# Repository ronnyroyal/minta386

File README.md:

# Minta 386 memory board

This is a reverse engineered memory board for the Minta Technologies PCB-305 Mainboard.  
https://theretroweb.com/motherboards/s/minta-technologies-co-pcb-305  
  
I bought this board a while ago missing it's proprietary memory board with the plan to reverse engineer the memory board.   
The memory card was designed with sipp memory in mind as i have a lot of sipp modules, but the spacing also allows for simm sockets to be installed.
 
It can accomodate up to 8 1MB modules with the slot being wired to theoretically support up to 16MB.  
The first PCB revision contains a fault with the parity bit lines being swapped. This is fixed in the provided files.

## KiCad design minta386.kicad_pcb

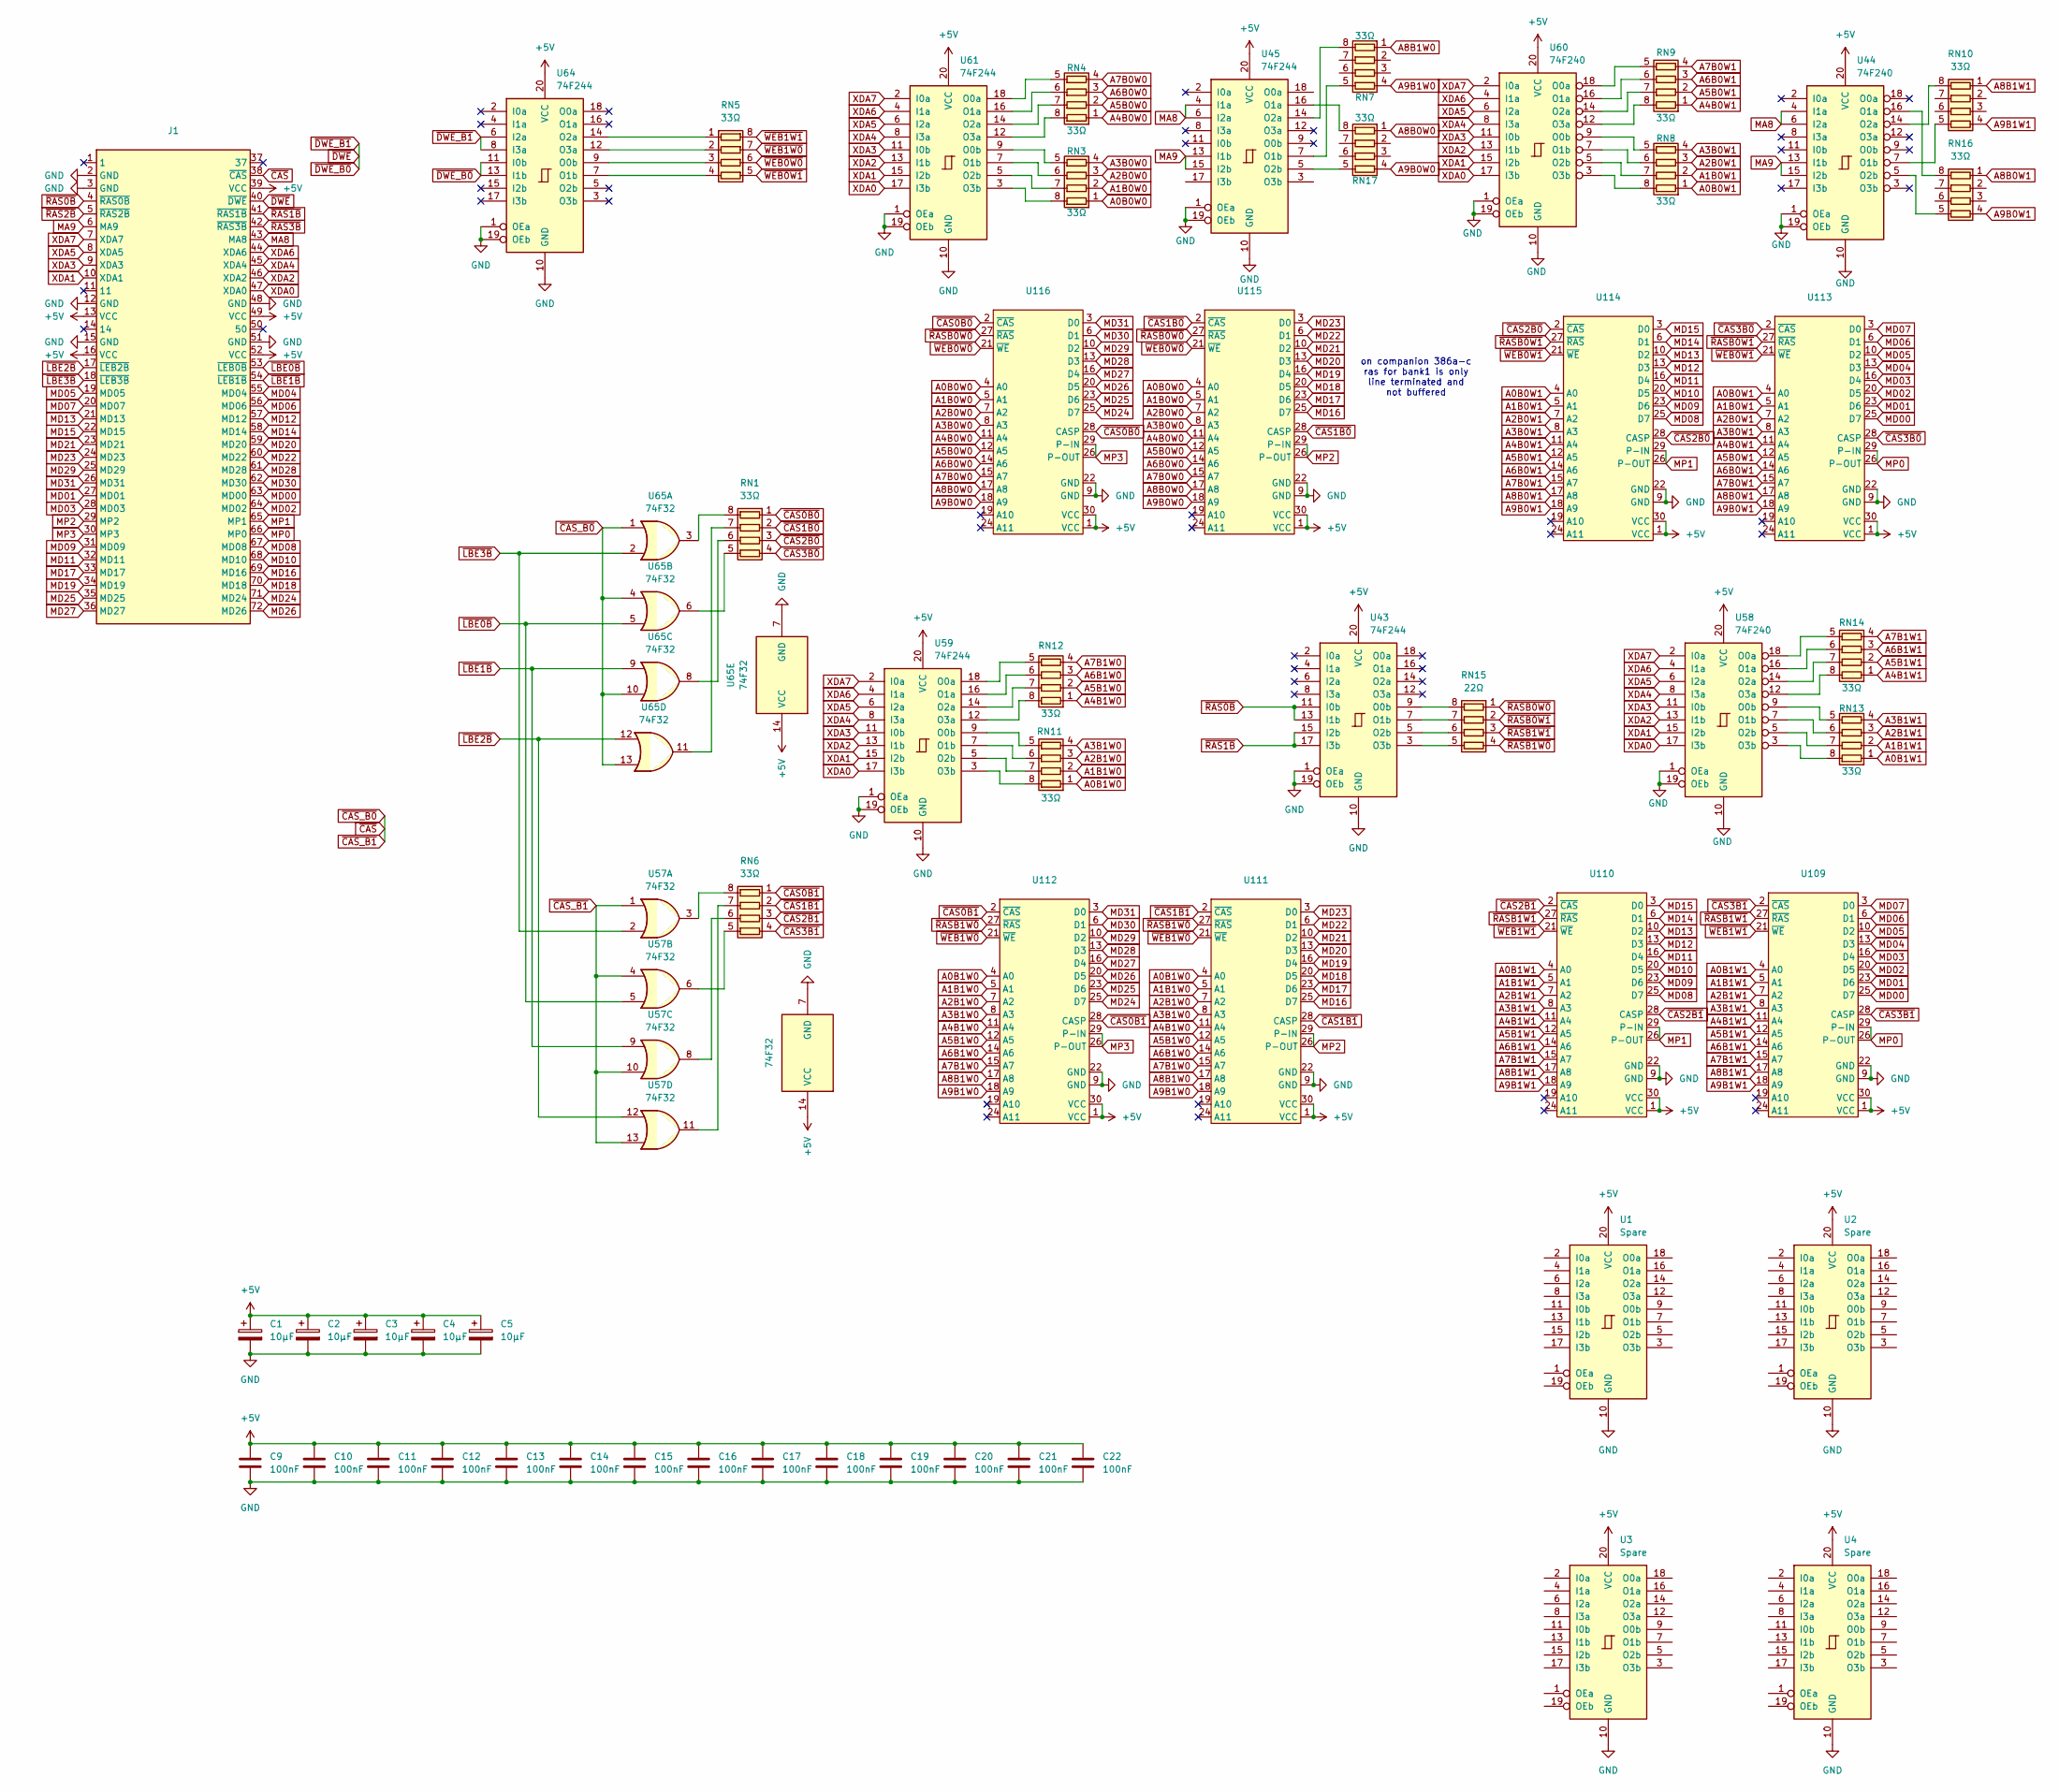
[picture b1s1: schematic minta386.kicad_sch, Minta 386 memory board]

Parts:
C1, C2, C3, C4, C5: 10µF; CP_EIA-6032-28_Kemet-C_Pad2.25x2.35mm_HandSolder
C9, C10, C11, C12, C13, C14, C15, C16, C17, C18, C19, C20, C21, C22: 100nF; C_0805_2012Metric_Pad1.18x1.45mm_HandSolder
J1: minta_386_memory_bus
RN1, RN3, RN4, RN5, RN6, RN7, RN8, RN9, RN10, RN11, RN12, RN13, RN14, RN16, RN17: 33Ω; R_Array_Concave_4x0603
RN15: 22Ω; R_Array_Concave_4x0603
U1, U2, U3, U4: Spare; SOIC-20W_7.5x12.8mm_P1.27mm
U43, U45, U59, U61, U64: 74F244; SOIC-20W_7.5x12.8mm_P1.27mm
U44, U58, U60: 74F240; SOIC-20W_7.5x12.8mm_P1.27mm
U57, U65: 74F32; SOIC-14_3.9x8.7mm_P1.27mm
U109, U110, U111, U112, U113, U114, U115, U116: PinSocket_1x30_P2.54mm_Vertical

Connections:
+5V: C1.1, C2.1, C3.1, C4.1, C5.1, C9.1, C10.1, C11.1, C12.1, C13.1, C14.1, C15.1, C16.1, C17.1, C18.1, C19.1, C20.1, C21.1, C22.1, J1.13 (VCC), J1.16 (VCC), J1.39 (VCC), J1.49 (VCC), J1.52 (VCC), U1.20 (VCC), U2.20 (VCC), U3.20 (VCC), U4.20 (VCC), U43.20 (VCC), U44.20 (VCC), U45.20 (VCC), U57.14 (VCC), U58.20 (VCC), U59.20 (VCC), U60.20 (VCC), U61.20 (VCC), U64.20 (VCC), U65.14 (VCC), U109.1 (VCC), U109.30 (VCC), U110.1 (VCC), U110.30 (VCC), U111.1 (VCC), U111.30 (VCC), U112.1 (VCC), U112.30 (VCC), U113.1 (VCC), U113.30 (VCC), U114.1 (VCC), U114.30 (VCC), U115.1 (VCC), U115.30 (VCC), U116.1 (VCC), U116.30 (VCC)
A0B0W0: RN3.1 (R1.1), U115.4 (A0), U116.4 (A0)
A0B0W1: RN8.1 (R1.1), U113.4 (A0), U114.4 (A0)
A0B1W0: RN11.1 (R1.1), U111.4 (A0), U112.4 (A0)
A0B1W1: RN13.1 (R1.1), U109.4 (A0), U110.4 (A0)
A1B0W0: RN3.2 (R2.1), U115.5 (A1), U116.5 (A1)
A1B0W1: RN8.2 (R2.1), U113.5 (A1), U114.5 (A1)
A1B1W0: RN11.2 (R2.1), U111.5 (A1), U112.5 (A1)
A1B1W1: RN13.2 (R2.1), U109.5 (A1), U110.5 (A1)
A2B0W0: RN3.3 (R3.1), U115.7 (A2), U116.7 (A2)
A2B0W1: RN8.3 (R3.1), U113.7 (A2), U114.7 (A2)
A2B1W0: RN11.3 (R3.1), U111.7 (A2), U112.7 (A2)
A2B1W1: RN13.3 (R3.1), U109.7 (A2), U110.7 (A2)
A3B0W0: RN3.4 (R4.1), U115.8 (A3), U116.8 (A3)
A3B0W1: RN8.4 (R4.1), U113.8 (A3), U114.8 (A3)
A3B1W0: RN11.4 (R4.1), U111.8 (A3), U112.8 (A3)
A3B1W1: RN13.4 (R4.1), U109.8 (A3), U110.8 (A3)
A4B0W0: RN4.1 (R1.1), U115.11 (A4), U116.11 (A4)
A4B0W1: RN9.1 (R1.1), U113.11 (A4), U114.11 (A4)
A4B1W0: RN12.1 (R1.1), U111.11 (A4), U112.11 (A4)
A4B1W1: RN14.1 (R1.1), U109.11 (A4), U110.11 (A4)
A5B0W0: RN4.2 (R2.1), U115.12 (A5), U116.12 (A5)
A5B0W1: RN9.2 (R2.1), U113.12 (A5), U114.12 (A5)
A5B1W0: RN12.2 (R2.1), U111.12 (A5), U112.12 (A5)
A5B1W1: RN14.2 (R2.1), U109.12 (A5), U110.12 (A5)
A6B0W0: RN4.3 (R3.1), U115.14 (A6), U116.14 (A6)
A6B0W1: RN9.3 (R3.1), U113.14 (A6), U114.14 (A6)
A6B1W0: RN12.3 (R3.1), U111.14 (A6), U112.14 (A6)
A6B1W1: RN14.3 (R3.1), U109.14 (A6), U110.14 (A6)
A7B0W0: RN4.4 (R4.1), U115.15 (A7), U116.15 (A7)
A7B0W1: RN9.4 (R4.1), U113.15 (A7), U114.15 (A7)
A7B1W0: RN12.4 (R4.1), U111.15 (A7), U112.15 (A7)
A7B1W1: RN14.4 (R4.1), U109.15 (A7), U110.15 (A7)
A8B0W0: RN17.1 (R1.1), U115.17 (A8), U116.17 (A8)
A8B0W1: RN16.1 (R1.1), U113.17 (A8), U114.17 (A8)
A8B1W0: RN7.1 (R1.1), U111.17 (A8), U112.17 (A8)
A8B1W1: RN10.1 (R1.1), U109.17 (A8), U110.17 (A8)
A9B0W0: RN17.4 (R4.1), U115.18 (A9), U116.18 (A9)
A9B0W1: RN16.4 (R4.1), U113.18 (A9), U114.18 (A9)
A9B1W0: RN7.4 (R4.1), U111.18 (A9), U112.18 (A9)
A9B1W1: RN10.4 (R4.1), U109.18 (A9), U110.18 (A9)
GND: C1.2, C2.2, C3.2, C4.2, C5.2, C9.2, C10.2, C11.2, C12.2, C13.2, C14.2, C15.2, C16.2, C17.2, C18.2, C19.2, C20.2, C21.2, C22.2, J1.2 (GND), J1.3 (GND), J1.12 (GND), J1.15 (GND), J1.48 (GND), J1.51 (GND), U1.10 (GND), U2.10 (GND), U3.10 (GND), U4.10 (GND), U43.1 (OEa), U43.10 (GND), U43.19 (OEb), U44.1 (OEa), U44.10 (GND), U44.19 (OEb), U45.1 (OEa), U45.10 (GND), U45.19 (OEb), U57.7 (GND), U58.1 (OEa), U58.10 (GND), U58.19 (OEb), U59.1 (OEa), U59.10 (GND), U59.19 (OEb), U60.1 (OEa), U60.10 (GND), U60.19 (OEb), U61.1 (OEa), U61.10 (GND), U61.19 (OEb), U64.1 (OEa), U64.10 (GND), U64.19 (OEb), U65.7 (GND), U109.9 (GND), U109.22 (GND), U110.9 (GND), U110.22 (GND), U111.9 (GND), U111.22 (GND), U112.9 (GND), U112.22 (GND), U113.9 (GND), U113.22 (GND), U114.9 (GND), U114.22 (GND), U115.9 (GND), U115.22 (GND), U116.9 (GND), U116.22 (GND)
MA8: J1.43 (MA8), U44.4 (I1a), U44.6 (I2a), U45.4 (I1a), U45.6 (I2a)
MA9: J1.6 (MA9), U44.13 (I1b), U44.15 (I2b), U45.13 (I1b), U45.15 (I2b)
MD00: J1.63 (MD00), U109.25 (D7), U113.25 (D7)
MD01: J1.27 (MD01), U109.23 (D6), U113.23 (D6)
MD02: J1.64 (MD02), U109.20 (D5), U113.20 (D5)
MD03: J1.28 (MD03), U109.16 (D4), U113.16 (D4)
MD04: J1.55 (MD04), U109.13 (D3), U113.13 (D3)
MD05: J1.19 (MD05), U109.10 (D2), U113.10 (D2)
MD06: J1.56 (MD06), U109.6 (D1), U113.6 (D1)
MD07: J1.20 (MD07), U109.3 (D0), U113.3 (D0)
MD08: J1.67 (MD08), U110.25 (D7), U114.25 (D7)
MD09: J1.31 (MD09), U110.23 (D6), U114.23 (D6)
MD10: J1.68 (MD10), U110.20 (D5), U114.20 (D5)
MD11: J1.32 (MD11), U110.16 (D4), U114.16 (D4)
MD12: J1.57 (MD12), U110.13 (D3), U114.13 (D3)
MD13: J1.21 (MD13), U110.10 (D2), U114.10 (D2)
MD14: J1.58 (MD14), U110.6 (D1), U114.6 (D1)
MD15: J1.22 (MD15), U110.3 (D0), U114.3 (D0)
MD16: J1.69 (MD16), U111.25 (D7), U115.25 (D7)
MD17: J1.33 (MD17), U111.23 (D6), U115.23 (D6)
MD18: J1.70 (MD18), U111.20 (D5), U115.20 (D5)
MD19: J1.34 (MD19), U111.16 (D4), U115.16 (D4)
MD20: J1.59 (MD20), U111.13 (D3), U115.13 (D3)
MD21: J1.23 (MD21), U111.10 (D2), U115.10 (D2)
MD22: J1.60 (MD22), U111.6 (D1), U115.6 (D1)
MD23: J1.24 (MD23), U111.3 (D0), U115.3 (D0)
MD24: J1.71 (MD24), U112.25 (D7), U116.25 (D7)
MD25: J1.35 (MD25), U112.23 (D6), U116.23 (D6)
MD26: J1.72 (MD26), U112.20 (D5), U116.20 (D5)
MD27: J1.36 (MD27), U112.16 (D4), U116.16 (D4)
MD28: J1.61 (MD28), U112.13 (D3), U116.13 (D3)
MD29: J1.25 (MD29), U112.10 (D2), U116.10 (D2)
MD30: J1.62 (MD30), U112.6 (D1), U116.6 (D1)
MD31: J1.26 (MD31), U112.3 (D0), U116.3 (D0)
MP0: J1.66 (MP0), U109.26 (P-OUT), U109.29 (P-IN), U113.26 (P-OUT), U113.29 (P-IN)
MP1: J1.65 (MP1), U110.26 (P-OUT), U110.29 (P-IN), U114.26 (P-OUT), U114.29 (P-IN)
MP2: J1.29 (MP2), U111.26 (P-OUT), U111.29 (P-IN), U115.26 (P-OUT), U115.29 (P-IN)
MP3: J1.30 (MP3), U112.26 (P-OUT), U112.29 (P-IN), U116.26 (P-OUT), U116.29 (P-IN)
unnamed: RN1.8 (R1.2), U65.3
unnamed: RN1.7 (R2.2), U65.11
unnamed: RN1.6 (R3.2), U65.8
unnamed: RN1.5 (R4.2), U65.6
unnamed: RN3.8 (R1.2), U61.3 (O3b)
unnamed: RN3.7 (R2.2), U61.5 (O2b)
unnamed: RN3.6 (R3.2), U61.7 (O1b)
unnamed: RN3.5 (R4.2), U61.9 (O0b)
unnamed: RN4.8 (R1.2), U61.12 (O3a)
unnamed: RN4.7 (R2.2), U61.14 (O2a)
unnamed: RN4.6 (R3.2), U61.16 (O1a)
unnamed: RN4.5 (R4.2), U61.18 (O0a)
unnamed: RN5.1 (R1.1), U64.14 (O2a)
unnamed: RN5.2 (R2.1), U64.12 (O3a)
unnamed: RN5.3 (R3.1), U64.9 (O0b)
unnamed: RN5.4 (R4.1), U64.7 (O1b)
unnamed: RN6.8 (R1.2), U57.3
unnamed: RN6.7 (R2.2), U57.11
unnamed: RN6.6 (R3.2), U57.8
unnamed: RN6.5 (R4.2), U57.6
unnamed: RN7.8 (R1.2), U45.14 (O2a)
unnamed: RN7.5 (R4.2), U45.7 (O1b)
unnamed: RN8.8 (R1.2), U60.3 (O3b)
unnamed: RN8.7 (R2.2), U60.5 (O2b)
unnamed: RN8.6 (R3.2), U60.7 (O1b)
unnamed: RN8.5 (R4.2), U60.9 (O0b)
unnamed: RN9.8 (R1.2), U60.12 (O3a)
unnamed: RN9.7 (R2.2), U60.14 (O2a)
unnamed: RN9.6 (R3.2), U60.16 (O1a)
unnamed: RN9.5 (R4.2), U60.18 (O0a)
unnamed: RN10.8 (R1.2), U44.14 (O2a)
unnamed: RN10.5 (R4.2), U44.7 (O1b)
unnamed: RN11.8 (R1.2), U59.3 (O3b)
unnamed: RN11.7 (R2.2), U59.5 (O2b)
unnamed: RN11.6 (R3.2), U59.7 (O1b)
unnamed: RN11.5 (R4.2), U59.9 (O0b)
unnamed: RN12.8 (R1.2), U59.12 (O3a)
unnamed: RN12.7 (R2.2), U59.14 (O2a)
unnamed: RN12.6 (R3.2), U59.16 (O1a)
unnamed: RN12.5 (R4.2), U59.18 (O0a)
unnamed: RN13.8 (R1.2), U58.3 (O3b)
unnamed: RN13.7 (R2.2), U58.5 (O2b)
unnamed: RN13.6 (R3.2), U58.7 (O1b)
unnamed: RN13.5 (R4.2), U58.9 (O0b)
unnamed: RN14.8 (R1.2), U58.12 (O3a)
unnamed: RN14.7 (R2.2), U58.14 (O2a)
unnamed: RN14.6 (R3.2), U58.16 (O1a)
unnamed: RN14.5 (R4.2), U58.18 (O0a)
unnamed: RN15.8 (R1.2), U43.9 (O0b)
unnamed: RN15.7 (R2.2), U43.7 (O1b)
unnamed: RN15.6 (R3.2), U43.5 (O2b)
unnamed: RN15.5 (R4.2), U43.3 (O3b)
unnamed: RN16.8 (R1.2), U44.16 (O1a)
unnamed: RN16.5 (R4.2), U44.5 (O2b)
unnamed: RN17.8 (R1.2), U45.16 (O1a)
unnamed: RN17.5 (R4.2), U45.5 (O2b)
XDA0: J1.47 (XDA0), U58.17 (I3b), U59.17 (I3b), U60.17 (I3b), U61.17 (I3b)
XDA1: J1.10 (XDA1), U58.15 (I2b), U59.15 (I2b), U60.15 (I2b), U61.15 (I2b)
XDA2: J1.46 (XDA2), U58.13 (I1b), U59.13 (I1b), U60.13 (I1b), U61.13 (I1b)
XDA3: J1.9 (XDA3), U58.11 (I0b), U59.11 (I0b), U60.11 (I0b), U61.11 (I0b)
XDA4: J1.45 (XDA4), U58.8 (I3a), U59.8 (I3a), U60.8 (I3a), U61.8 (I3a)
XDA5: J1.8 (XDA5), U58.6 (I2a), U59.6 (I2a), U60.6 (I2a), U61.6 (I2a)
XDA6: J1.44 (XDA6), U58.4 (I1a), U59.4 (I1a), U60.4 (I1a), U61.4 (I1a)
XDA7: J1.7 (XDA7), U58.2 (I0a), U59.2 (I0a), U60.2 (I0a), U61.2 (I0a)
~CAS0B0: RN1.1 (R1.1), U116.2 (~CAS), U116.28 (CASP)
~CAS0B1: RN6.1 (R1.1), U112.2 (~CAS), U112.28 (CASP)
~CAS1B0: RN1.2 (R2.1), U115.2 (~CAS), U115.28 (CASP)
~CAS1B1: RN6.2 (R2.1), U111.2 (~CAS), U111.28 (CASP)
~CAS2B0: RN1.3 (R3.1), U114.2 (~CAS), U114.28 (CASP)
~CAS2B1: RN6.3 (R3.1), U110.2 (~CAS), U110.28 (CASP)
~CAS3B0: RN1.4 (R4.1), U113.2 (~CAS), U113.28 (CASP)
~CAS3B1: RN6.4 (R4.1), U109.2 (~CAS), U109.28 (CASP)
~CAS_B0: J1.38 (~CAS), U57.1, U57.4, U57.10, U57.13, U65.1, U65.4, U65.10, U65.13
~DWE_B0: J1.40 (~DWE), U64.6 (I2a), U64.8 (I3a), U64.11 (I0b), U64.13 (I1b)
~LBE0B: J1.53 (~LEB0B), U57.5, U65.5
~LBE1B: J1.54 (~LEB1B), U57.9, U65.9
~LBE2B: J1.17 (~LEB2B), U57.12, U65.12
~LBE3B: J1.18 (~LEB3B), U57.2, U65.2
~RAS0B: J1.4 (~RAS0B), U43.11 (I0b), U43.13 (I1b)
~RAS1B: J1.41 (~RAS1B), U43.15 (I2b), U43.17 (I3b)
~RAS2B: J1.5 (~RAS2B)
~RAS3B: J1.42 (~RAS3B)
~RASB0W0: RN15.1 (R1.1), U115.27 (~RAS), U116.27 (~RAS)
~RASB0W1: RN15.2 (R2.1), U113.27 (~RAS), U114.27 (~RAS)
~RASB1W0: RN15.4 (R4.1), U111.27 (~RAS), U112.27 (~RAS)
~RASB1W1: RN15.3 (R3.1), U109.27 (~RAS), U110.27 (~RAS)
~WEB0W0: RN5.6 (R3.2), U115.21 (~WE), U116.21 (~WE)
~WEB0W1: RN5.5 (R4.2), U113.21 (~WE), U114.21 (~WE)
~WEB1W0: RN5.7 (R2.2), U111.21 (~WE), U112.21 (~WE)
~WEB1W1: RN5.8 (R1.2), U109.21 (~WE), U110.21 (~WE)

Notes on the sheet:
on companion 386a-c ras for bank1 is only line terminated and not buffered

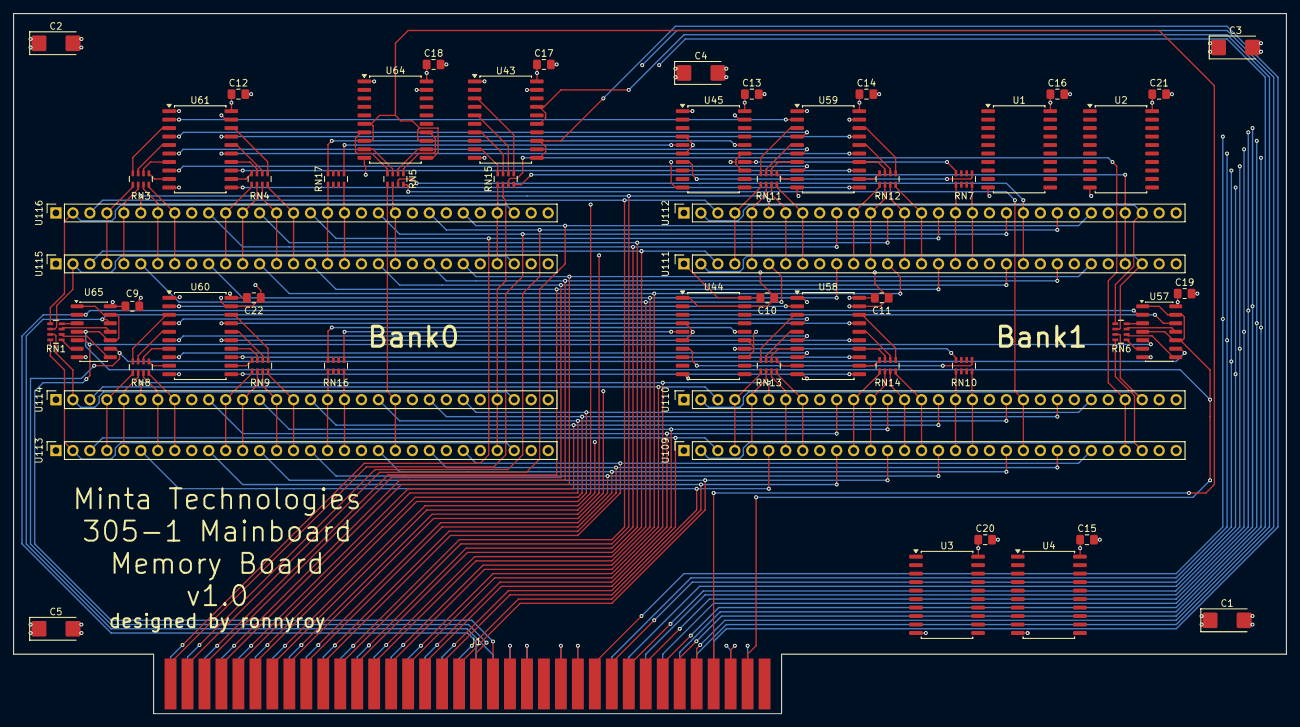
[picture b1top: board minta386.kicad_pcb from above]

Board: 4 copper layers, 190.5 x 104.8 mm, 58 parts (0 on the bottom side), 168 nets.

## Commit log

2025-10-25 Add initial protoype PCB files with parity bit error fixed
2025-10-25 Add mainboard image
2025-10-25 Create README for Minta 386 memory board project
    Added a README file for the Minta 386 memory board project, detailing its purpose and specifications.
2025-11-06 add card images
2025-11-06 link images and add TRW link
2025-11-06 slight board chnages for rev 1.0
